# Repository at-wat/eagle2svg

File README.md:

# eagle2svg
Eagle cad to SVG converter.

eagle2svg helps social coding based circuit development.
It is easy to upload and embed drawings to the pull-request comment
by using [gh-pr-comment](https://github.com/at-wat/gh-pr-comment).

## Install

```
$ pip install --user eagle2svg
```

## Usage

```
eagle2svg eagle-file [sheet# [layer# [layer# ...]]]
```

- sheet#: schematic sheet index (for board layout rendering, set 0)
  - default: `0`
- layer#: visible layer index
  - default: `1 16 17 18 19 20 21 22 25 26 29 30 91 92 93 94 95 96 97 104`
  - e.g. board top layers: `1 20 17 18 21 25 19`
  - e.g. board bottom layers: `16 20 17 18 22 26 19`

## License

This package is released under BSD license.

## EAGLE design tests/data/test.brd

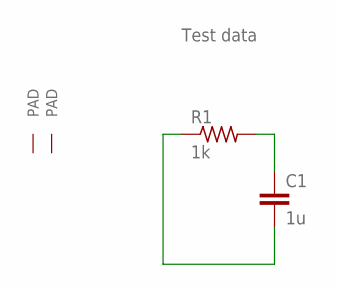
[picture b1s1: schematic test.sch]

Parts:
C1: 1u; C0402
PAD1: PADLONG; LONG
PAD2: PADOFFSET; OFFSET
R1: 1k; R0402

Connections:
unnamed: C1.1, R1.2
unnamed: C1.2, R1.1

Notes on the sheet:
Test data

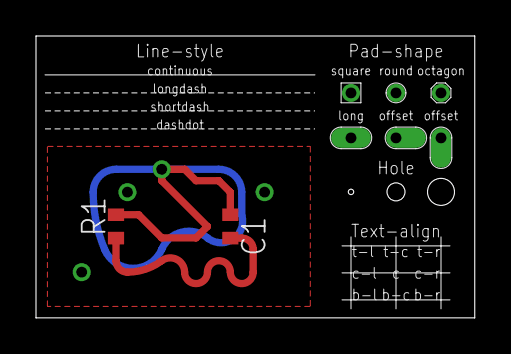
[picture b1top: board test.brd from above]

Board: 2 copper layers, 24.4 x 15.7 mm, 5 parts (0 on the bottom side), 2 nets.

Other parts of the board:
PAD3: PADOFFSET; OFFSET

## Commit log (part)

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2017-11-18 Initial drop.
2017-11-18 Split code.
2017-11-18 Fix repository uri.
2017-11-18 Add board rendering.
2017-11-18 Support curved line and polygon.
2017-11-18 Fix text alignment.
2017-11-18 Support square pad.
2017-11-18 Fix layer z-index.
2017-11-18 Modify text baseline.
2017-11-18 Add install and exec test.
2017-11-18 Fix python3 install.
2017-11-19 Add install and exec test. (#1)
2017-11-19 Fix passing command line arguments.
2017-11-19 Fix test.
2017-11-19 Fix permission.
2017-11-19 Fix for py3.
2017-11-19 Fix bot comment.
2017-11-19 Fix passing command line arguments. (#2)
    * Fix passing command line arguments.
    * Fix test.
    * Fix for python 3.
2017-11-19 Increment version to 0.1.0.dev1.
2017-11-19 Fix coding styles.
2017-11-19 Add coding style check.
2017-11-19 Fix splitted str.
2017-11-19 Fix bot.
2017-11-19 Fix bot load and coding style.
2017-11-19 Add style errors.
2017-11-19 Install style check tools.
2017-11-19 Check style before install.
2017-11-19 Fix style error output.
2017-11-19 Fix lint errors.
2017-11-19 Fix coding styles. (#3)
    * Fix coding styles.
    * Add coding style check and lint.
2017-11-19 Increment version to 0.1.0.dev1. (#4)
2017-11-19 Fix document size and background.
2017-11-19 Update gh-pr-comment and comment rendering result images.
2017-11-19 Update gh-pr-comment and comment rendering result images. (#5)
2017-11-19 Upload images only on PR.
2017-11-19 Fix branch build.
2017-11-19 Upload images only on PR. (#6)
2017-11-19 Fix background color.
2017-11-19 Fix document size and background. (#7)
2017-11-23 Increment version to 0.1.1.
2017-11-23 Increment version to 0.1.1. (#8)
2017-11-23 Fix parsing long pin. (default length)
2017-11-23 Fix mirrored curve direction.
2017-11-23 Fix parsing long pin. (default length) (#9)
2017-11-23 Fix mirrored curve direction. (#10)
2017-11-23 Support octagon pad.
2017-11-23 Add octagon via in test data.
2017-11-23 Fix test data.
2017-11-23 Support octagon pad. (#11)
    * Support octagon pad.
    * Add octagon via in test data.
2017-11-25 Add README.
2017-11-25 Add README. (#12)
2018-01-06 Update test to detect text align error
2018-01-06 Treat align 'center' as 'center-center'
2018-01-06 Fix text center align (#14)
    * Update test to detect text align error
    * Treat align 'center' as 'center-center'
2018-01-06 Increment version to 0.1.2
2018-01-06 Increment version to 0.1.2 (#15)
2018-01-20 Update test data
2018-01-20 Render long and offset pad
    also fix pad rotate
2018-01-20 Fix lint error
2018-01-20 Add rotated pad to test data
2018-01-20 Support long pad (#17)
    * Render long and offset pad
    * Fix pad rotate
    * Update test data
    * Add rotated pad to test data
2018-01-20 Fix pad rotate handling
2018-01-20 Fix pad rotate handling (#18)
2018-01-20 Increment version to 0.1.3
2018-01-20 Increment version to 0.1.3 (#19)
2018-09-17 Add test for replacement
2018-09-17 Fix replace key
2018-09-17 Fix text replace (#22)
    * Add test for replacement
    * Fix replace key
2018-09-17 Increment version to 0.1.4
2018-09-17 Increment version to 0.1.4 (#23)
2019-06-07 Support duplicated library definition
2019-06-07 Add duplicated library in test data
2019-06-07 Fix test data
2019-06-07 Revert "Fix test data"
    This reverts commit 5b3889d491a62ed25f59e11b63b025891b0d1b8c.
2019-06-07 Support duplicated library definition (#27)
2019-06-07 Deploy only from python3.6 job
2019-06-07 Deploy only from python3.6 job (#28)
2020-11-30 Migrate to GitHub Actions
2020-11-30 Fix workflow
2020-11-30 Split deploy and test
2020-11-30 Fix scripts
2020-11-30 Fix path
2020-11-30 Add sleep after bot comment
2020-11-30 Hide old comments
2020-11-30 Migrate to GitHub Actions (#30)
2023-10-12 fix crash when float rotation
2023-10-13 Fix crash when float rotation (#32)
2023-10-13 Add renovate.json
2023-10-13 Add renovate.json (#33)
2023-10-13 Update actions/checkout action to v4
2023-10-13 Update actions/checkout action to v4 (#35)
2023-10-13 Update pypa/gh-action-pypi-publish action to v1.8.10 (#34)
2023-10-13 Update actions/setup-python action to v4
2023-10-13 Update actions/setup-python action to v4 (#37)
2023-10-13 Test on all supported python version
2023-10-13 Add pyproject.toml for py3.12
2023-10-13 Remove setup.py
2023-10-13 Revert "Remove setup.py"
    This reverts commit 9d1c27a3c9cb6e7c1eb225683068320742e68d46.
2023-10-13 Update CI script
2023-10-13 Revert "Revert "Remove setup.py""
    This reverts commit fb514f60642c9f39a1ee1b5361a9debfa79c5f75.
2023-10-13 Decrease min python version
2023-10-13 Use setup-gh-pr-comment action
2023-10-13 Shrink bot comment
2023-10-13 Adjust bot comment
2023-10-13 Migrate to pyproject.toml and test on all supported python versions (#38)
2023-10-13 Bump version to 0.1.5
2023-10-13 Bump version to 0.1.5 (#39)
2023-10-13 Fix CI
2023-10-13 Fix step name
2023-10-13 Fix CI (#40)
2023-12-06 Update actions/setup-python action to v5
2024-09-02 Update pypa/gh-action-pypi-publish action to v1.10.0 (#41)
2024-09-02 Update actions/setup-python action to v5 (#42)
2025-08-11 Update actions/checkout action to v5
2025-08-12 Update actions/checkout action to v5 (#44)
2025-08-12 Update pypa/gh-action-pypi-publish action to v1.12.4 (#43)
2025-09-04 Update actions/setup-python action to v6
2025-09-04 Bump pypa/gh-action-pypi-publish in /.github/workflows
    Bumps [pypa/gh-action-pypi-publish](https://github.com/pypa/gh-action-pypi-publish) from 1.12.4 to 1.13.0.
    - [Release notes](https://github.com/pypa/gh-action-pypi-publish/releases)
    - [Commits](https://github.com/pypa/gh-action-pypi-publish/compare/v1.12.4...v1.13.0)
    ---
    updated-dependencies:
    - dependency-name: pypa/gh-action-pypi-publish
2025-09-08 Bump pypa/gh-action-pypi-publish in /.github/workflows (#47)
    Bumps [pypa/gh-action-pypi-publish](https://github.com/pypa/gh-action-pypi-publish) from 1.12.4 to 1.13.0.
    - [Release notes](https://github.com/pypa/gh-action-pypi-publish/releases)
    - [Commits](https://github.com/pypa/gh-action-pypi-publish/compare/v1.12.4...v1.13.0)
    ---
    updated-dependencies:
    - dependency-name: pypa/gh-action-pypi-publish
2025-09-08 Update actions/setup-python action to v6 (#46)
2025-11-20 Update actions/checkout action to v6
2026-05-07 Fix lint CI job
2026-05-07 Fix CI permissions
2026-05-07 Disable hide-old-bot-comments job on fork
2026-05-08 Disable hide-old-bot-comments job on fork (#53)
2026-06-18 Update actions/checkout action to v7
